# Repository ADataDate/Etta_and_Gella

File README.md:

Hardware project collaborations by Etta and Gella
=================================================================
Repository Contents
-------------------
* **/Bat** - wearable bat badge created for Fashion Hacking for Augmented Identity workshop SXSW 2019 
* **/BigBat** - large bat shaped development board prototype
* **/Diamond** - modular wearable hardware prototype for Designing Expressive Modular Hardware workshop Hackaday Superconference 2019
 
Released under: `https://creativecommons.org/licenses/by-nc-sa/4.0/legalcode

This license lets others remix, tweak, and build upon your work
non-commercially, and although their new works must also 
acknowledge you and be non-commercial, they don’t have to
 license their derivative works on the same terms.

Keep in touch with us:
* Mary [@_LightningHawk](https://twitter.com/_LightningHawk), https://www.ettawest.com
* Angela [@the_gella](https://twitter.com/the_gella), https://gellacraft.com

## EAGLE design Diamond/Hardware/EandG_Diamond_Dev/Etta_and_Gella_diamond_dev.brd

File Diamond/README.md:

Designing Expressive Modular Wearable Hardware
with Etta and Gella @ Hackaday Superconference November 2, 2018 

=================================================================

Repository Contents
-------------------
* **/Firmware** - Example code 
* **/Hardware** - Eagle design files (.brd, .sch)
* **/Spreadsheets** - BOM, parts and boards tracking, etc.
* **/Graphics** - Brainstorming images, sketches, laser files
 
Released under: `https://creativecommons.org/licenses/by-nc-sa/4.0/legalcode

This license lets others remix, tweak, and build upon your work
non-commercially, and although their new works must also 
acknowledge you and be non-commercial, they don’t have to
 license their derivative works on the same terms.

[Workshop slides](https://docs.google.com/presentation/d/1X1z0bJy7SYfVST1Kgu7OEDOKLFOzCg2_WMVUaLJVd0Q/edit?usp=sharing)

Keep in touch with us:
* Mary [@_LightningHawk](https://twitter.com/_LightningHawk), https://www.ettawest.com
* Angela [@the_gella](https://twitter.com/the_gella), https://gellacraft.com

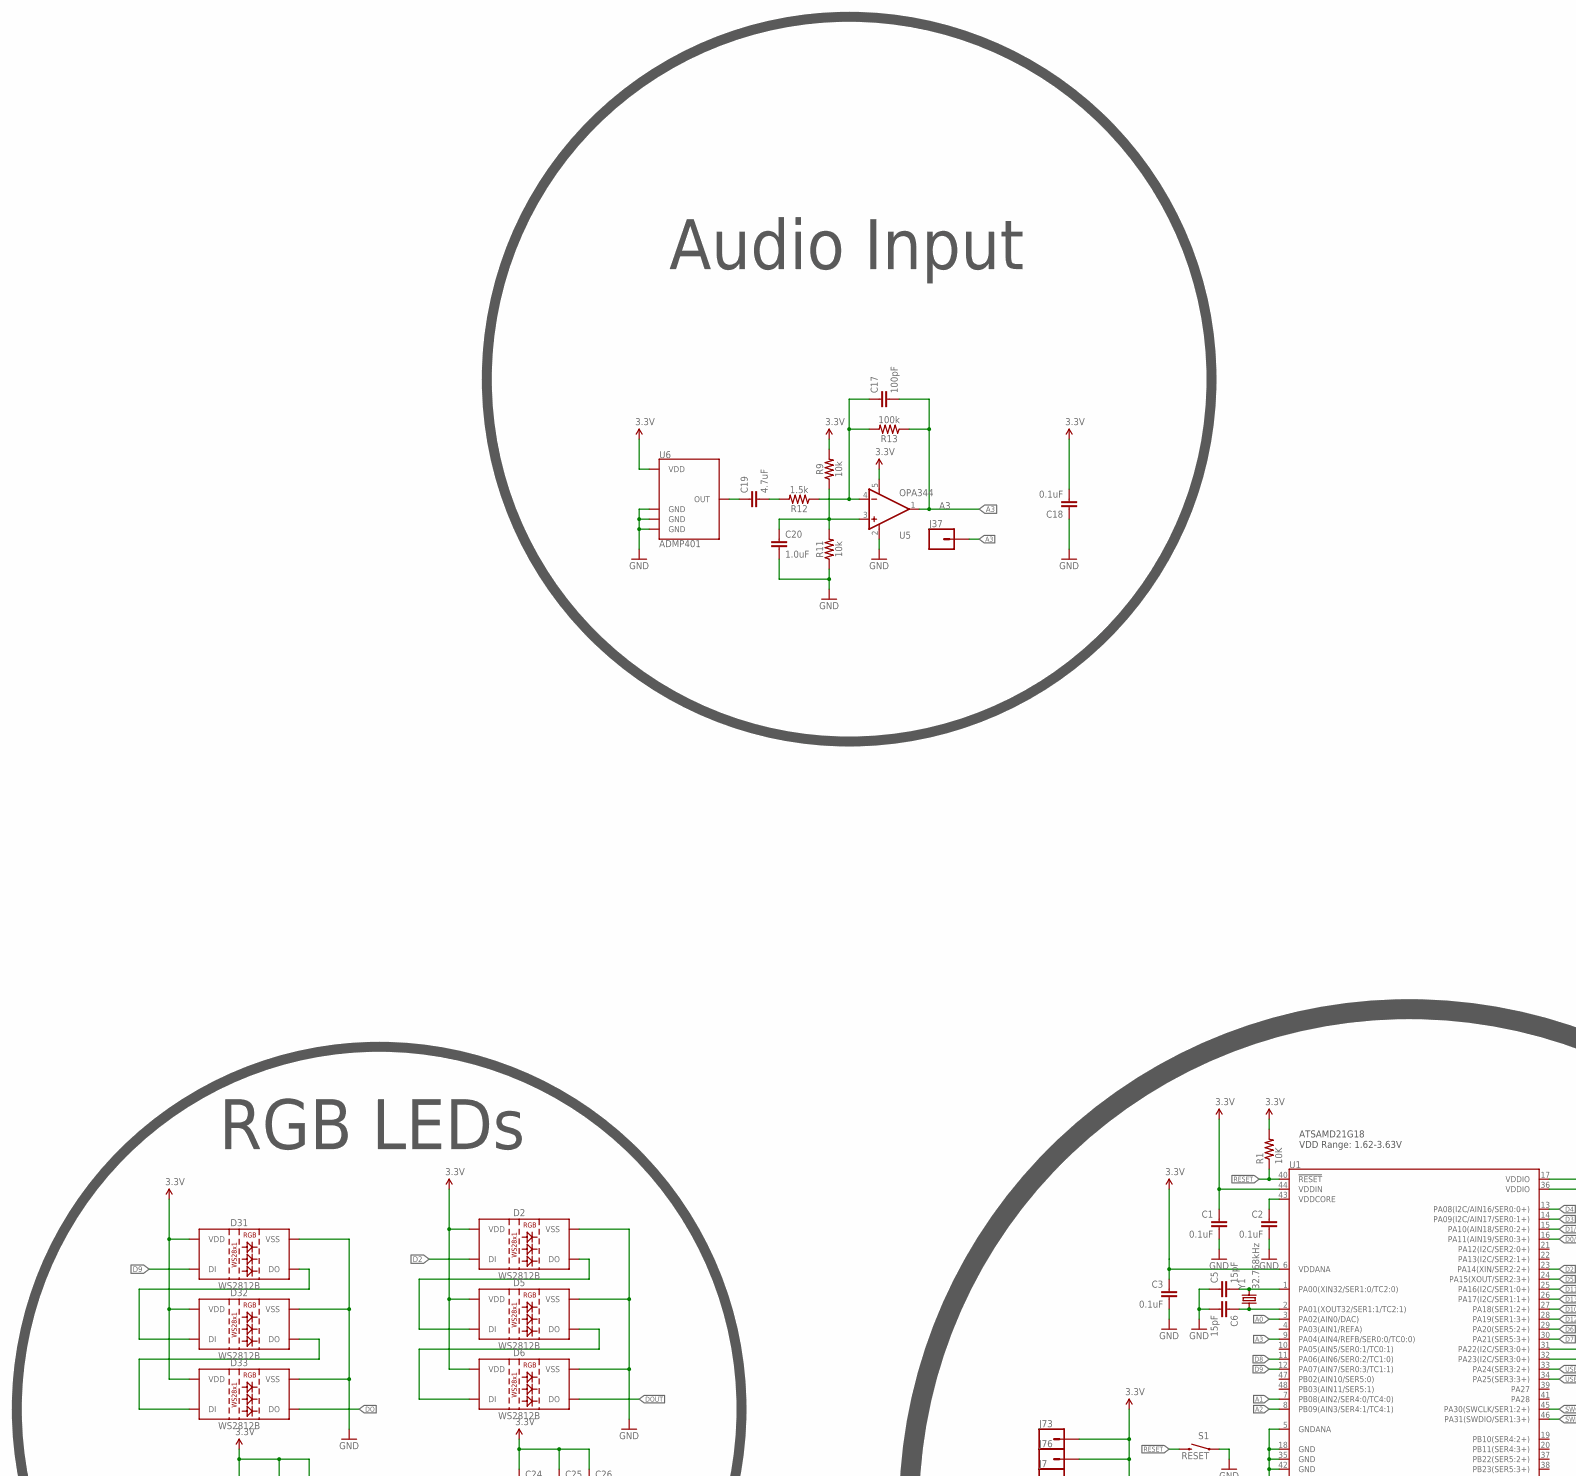
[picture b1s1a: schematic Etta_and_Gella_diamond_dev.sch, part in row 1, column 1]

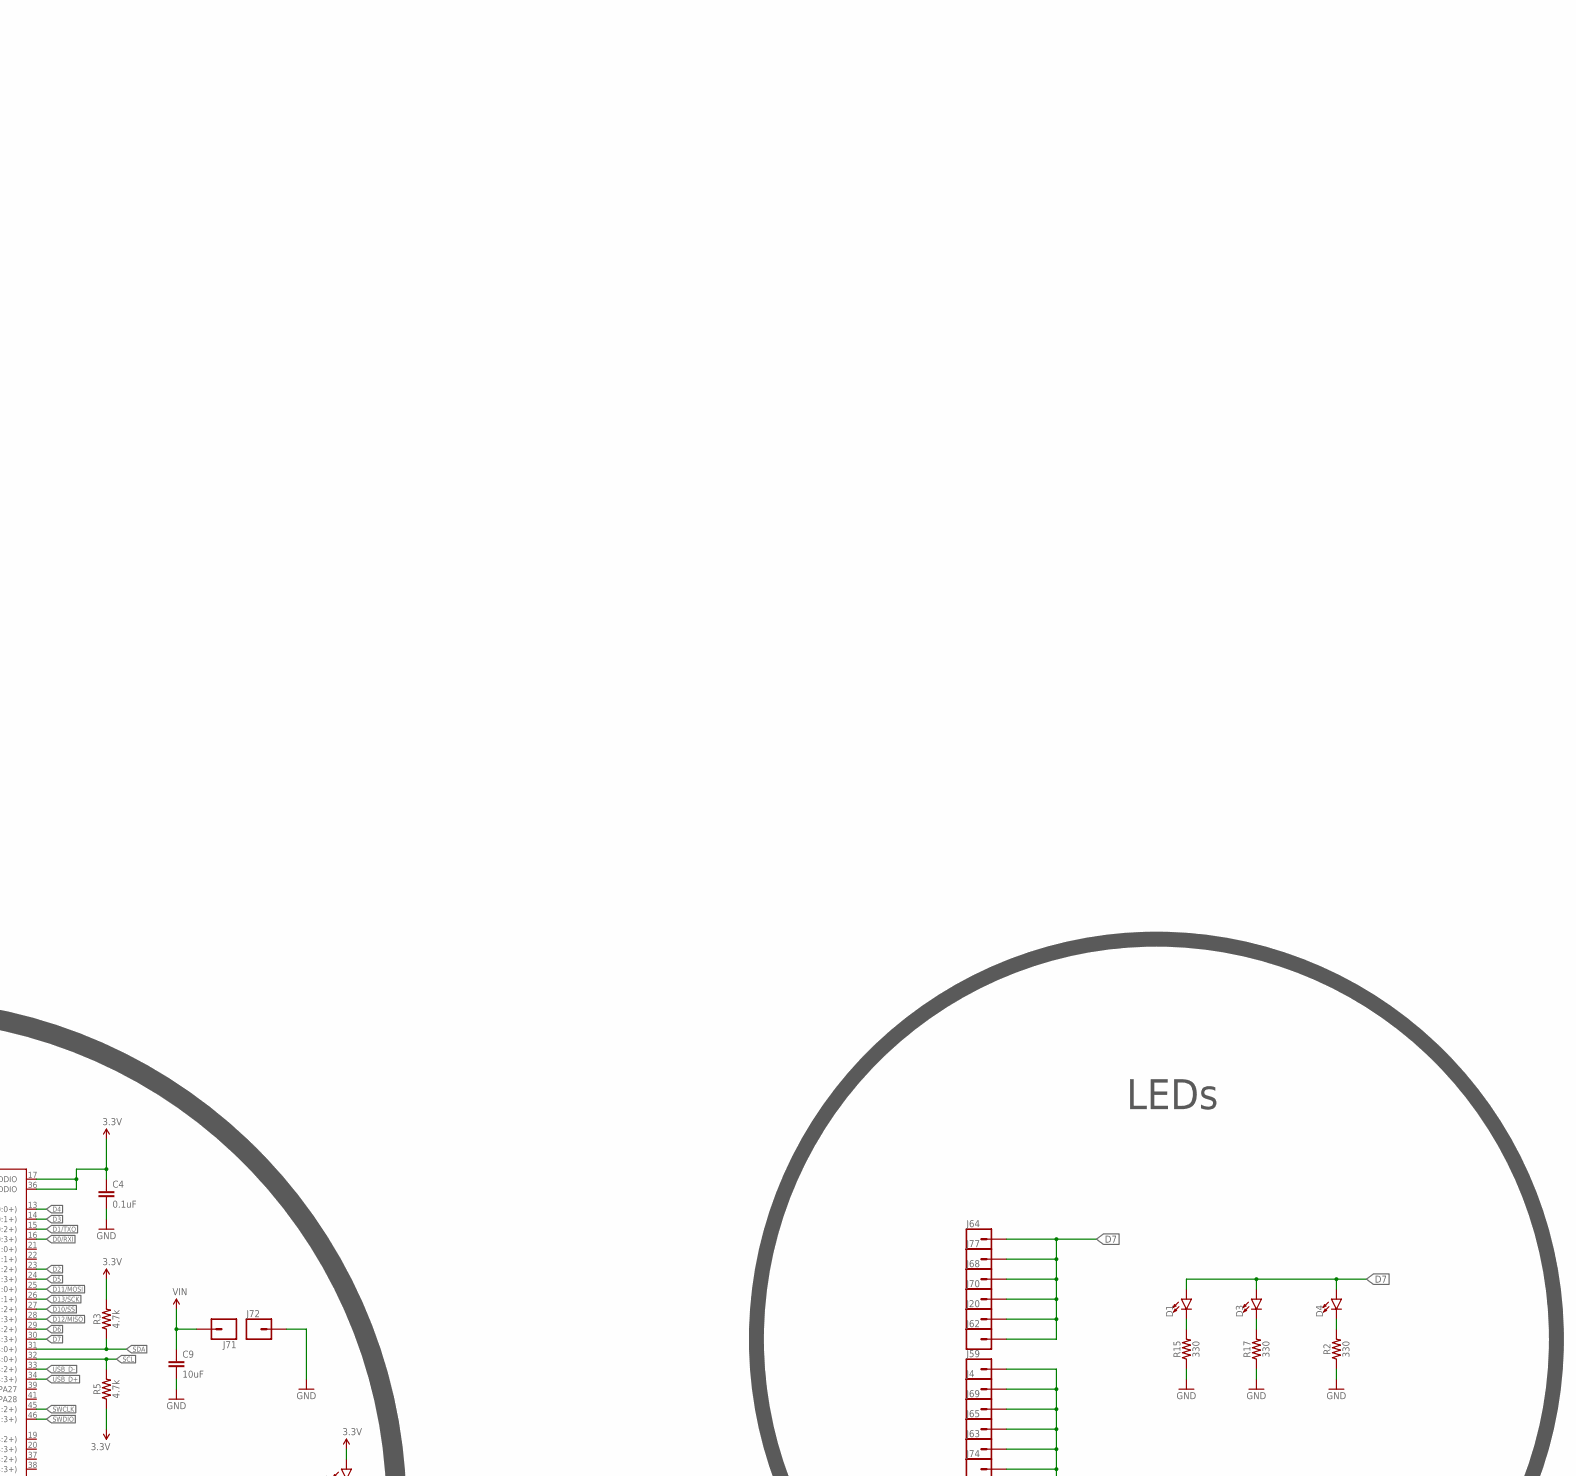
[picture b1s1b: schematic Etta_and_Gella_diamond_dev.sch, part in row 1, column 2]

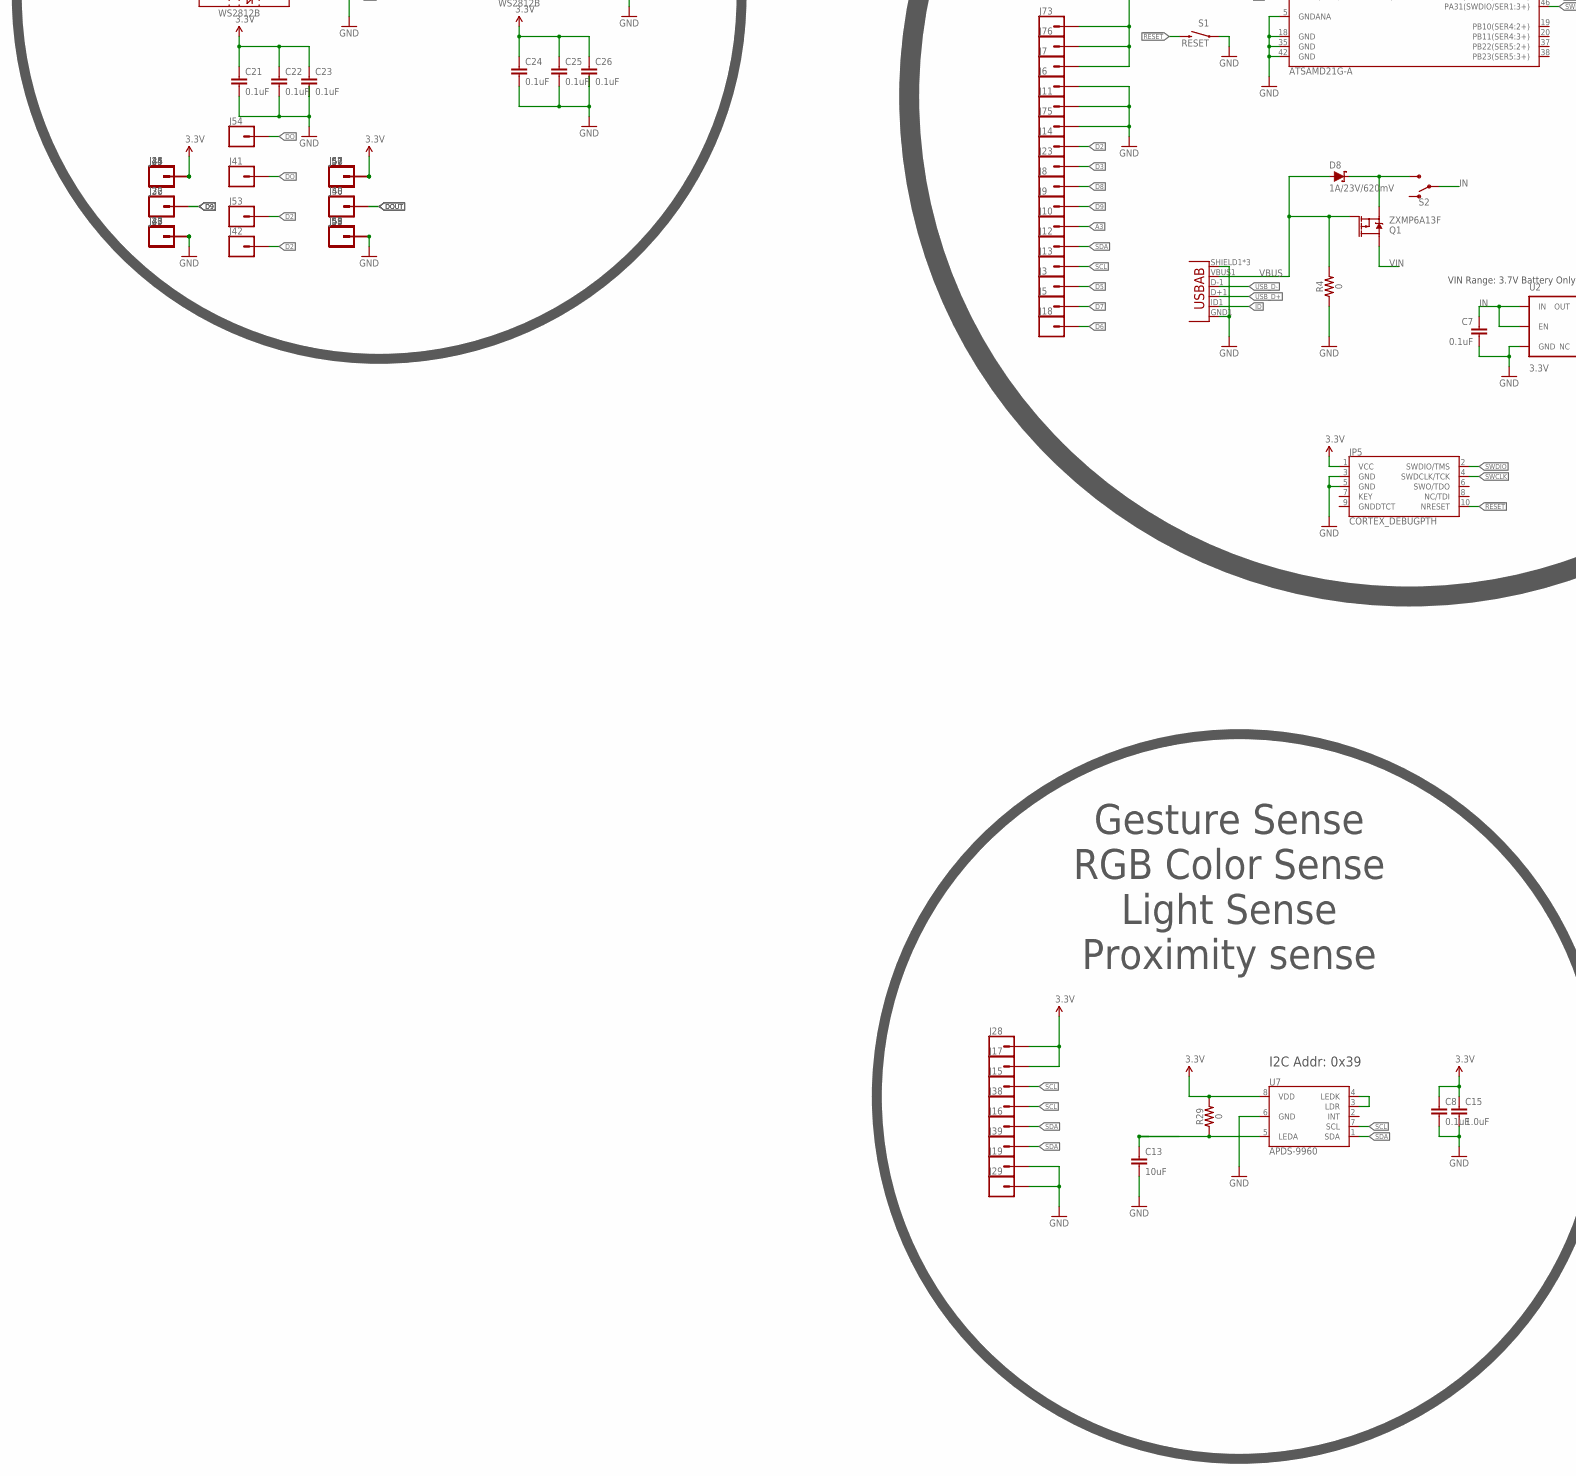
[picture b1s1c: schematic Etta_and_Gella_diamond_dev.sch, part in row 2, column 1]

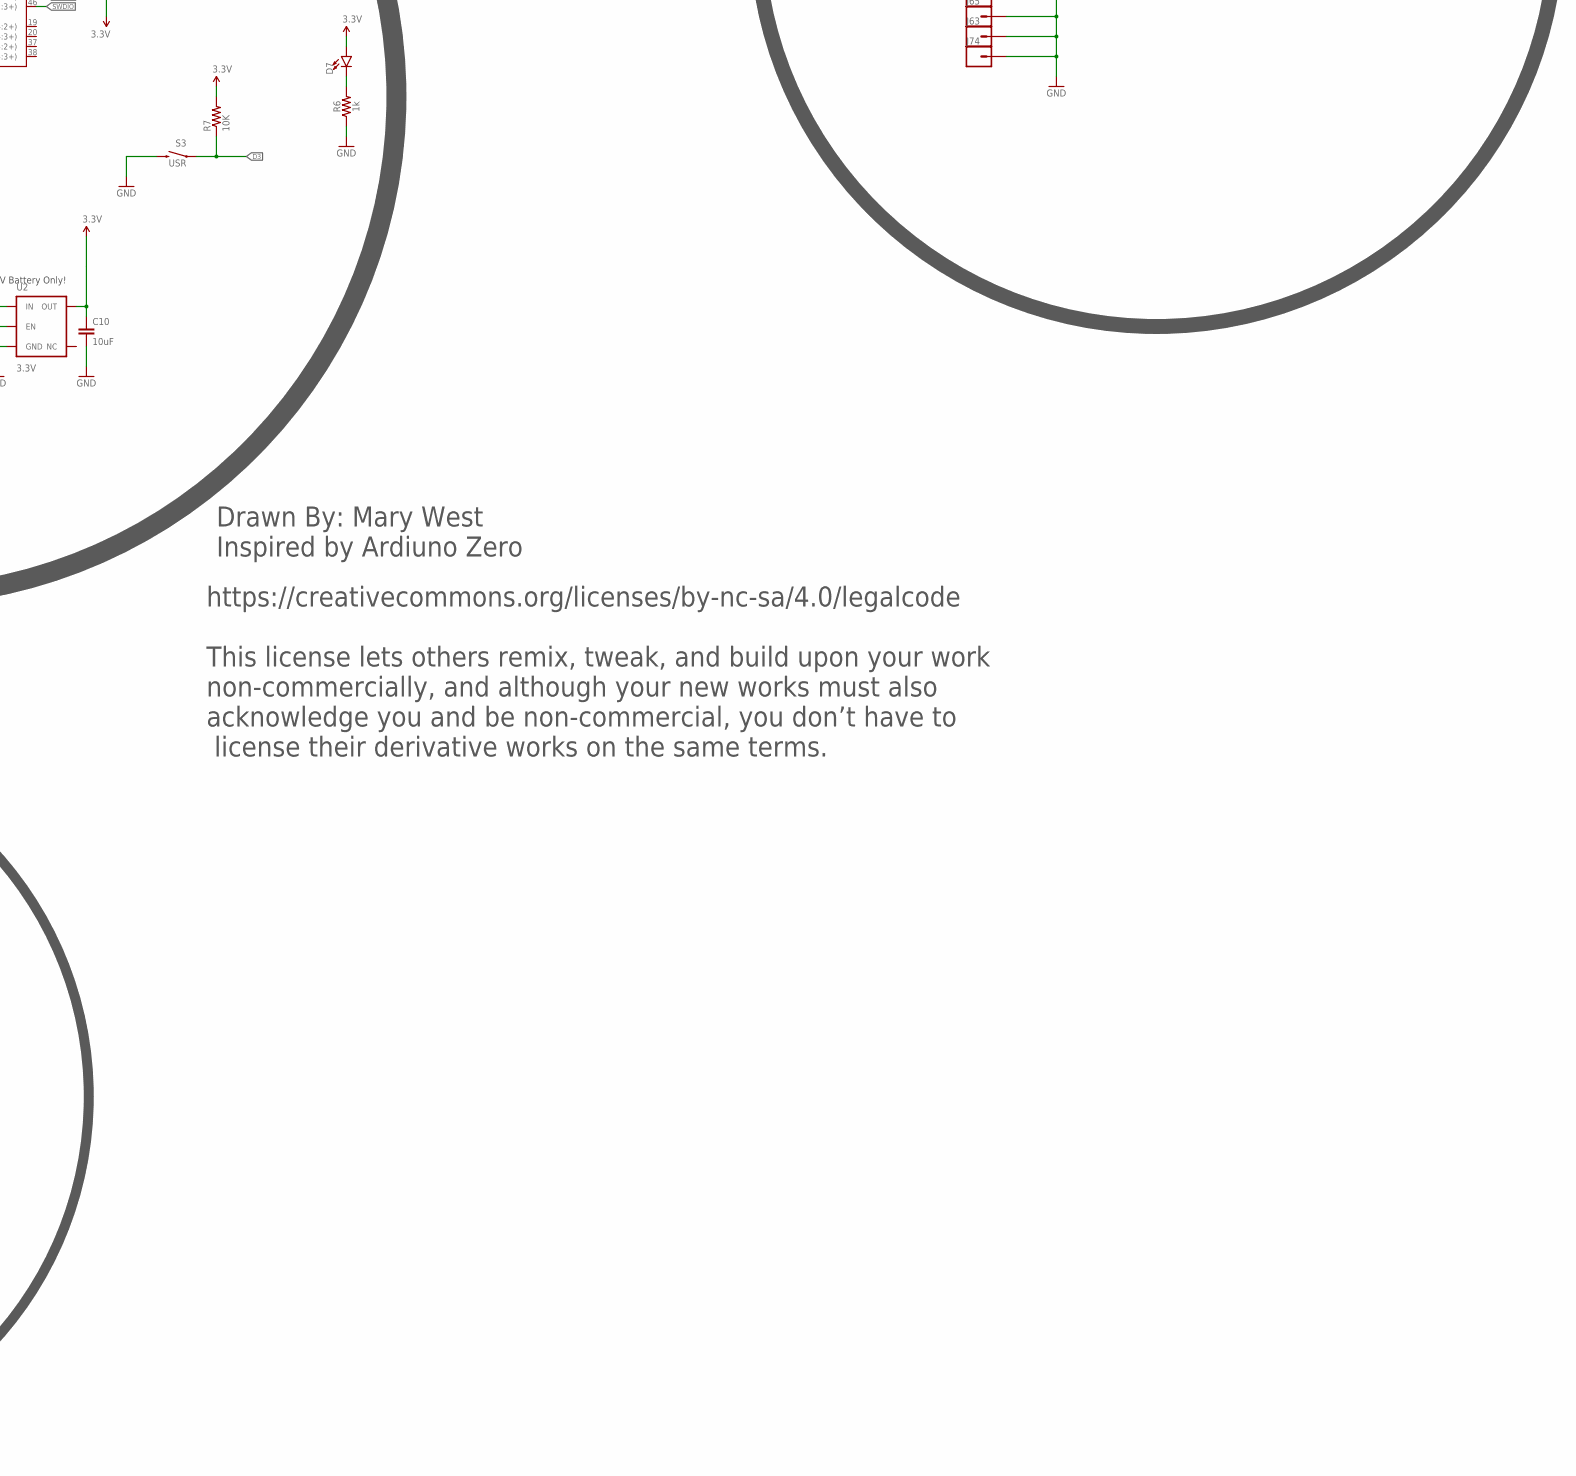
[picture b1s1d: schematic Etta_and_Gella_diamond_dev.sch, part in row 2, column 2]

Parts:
C1, C2, C3, C4, C7, C8, C18, C21, C22, C23, C24, C25, C26: 0.1uF; 0603
C5, C6: 15pF; 0603
C9, C10: 10uF; 0603
C13: 10uF; 0805
C15, C20: 1.0uF; 0603
C17: 100pF; 0603
C19: 4.7uF; 0603
D1, D3, D4, D7: LED1206; LED-1206
D2, D5, D6, D31, D32, D33: WS2812B
D8: 1A/23V/620mV; SOD-323
J3, J4, J5, J6, J7, J8, J9, J10, J11, J12, J13, J14, J15, J16, J17, J18, J19, J20, J23, J25, J26, J27, J28, J29, J32, J33, J34, J37, J38, J39, J41, J42, J43, J44, J45, J46, J47, J48, J49, J50, J51, J52, J53, J54, J55, J56, J57, J58, J59, J62, J63, J64, J65, J68, J69, J70, J71, J72, J73, J74, J75, J76, J77: CONN_01; 1X01
JP3: USB-ABCONN-11794; USB-AB-MICRO-SMD_V03
JP5: CORTEX_DEBUGPTH; 2X5-PTH-1.27MM
Q1: ZXMP6A13F; SOT23-3
R1, R7: 10K; 0603-RES@1
R2, R15, R17: 330; 0603
R3, R5: 4.7k; 0603
R4, R29: 0; 0603
R6: 1k; 0603
R9, R11: 10k; 0603
R12: 1.5k; 0603
R13: 100k; 0603
S1: RESET; TACTILE_SWITCH_SMD_4.6X2.8MM
S2: SWITCH-SPDT-SMD-AYZ0202; SWITCH_DPDT_SMD_AYZ0202
S3: USR; TACTILE_SWITCH_SMD_4.6X2.8MM
U1: ATSAMD21G-A; TQFP-48
U2: 3.3V; SOT23-5
U5: OPA344; SOT23-5
U6: ADMP401
U7: APDS-9960
Y1: 32.768kHz; CRYSTAL-SMD-3.2X1.5MM

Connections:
3.3V: C1.1, C3.1, C4.1, C8.1, C10.1, C15.1, C18.2, C21.1, C22.1, C23.1, C24.1, C25.1, C26.1, D2.1 (VDD), D5.1 (VDD), D6.1 (VDD), D7.A, D31.1 (VDD), D32.1 (VDD), D33.1 (VDD), J7.P$1, J17.P$1, J25.P$1, J28.P$1, J34.P$1, J44.P$1, J45.P$1, J47.P$1, J52.P$1, J56.P$1, J57.P$1, J73.P$1, J76.P$1, JP5.1 (VCC), R1.2, R3.2, R5.1, R7.2, R9.2, R29.2, U1.6 (VDDANA), U1.17 (VDDIO), U1.36 (VDDIO), U1.44 (VDDIN), U2.5 (OUT), U5.5 (V+), U6.5 (VDD), U7.8 (VDD)
!RESET: JP5.10 (NRESET), R1.1, S1.3 (2), S1.4 (2), U1.40 (!RESET!)
A0: U1.3 (PA02(AIN0/DAC))
A1: U1.7 (PB08(AIN2/SER4:0/TC4:0))
A2: U1.8 (PB09(AIN3/SER4:1/TC4:1))
A3: C17.2, J10.P$1, J37.P$1, R13.1, U1.9 (PA04(AIN4/REFB/SER0:0/TC0:0)), U5.1 (OUT)
D0/RXI: U1.16 (PA11(AIN19/SER0:3+))
D1/TXO: U1.15 (PA10(AIN18/SER0:2+))
D2: D2.4 (DI), J14.P$1, J42.P$1, J53.P$1, U1.23 (PA14(XIN/SER2:2+))
D3: J23.P$1, R7.1, S3.1, S3.2 (1), U1.14 (PA09(I2C/AIN17/SER0:1+))
D4: U1.13 (PA08(I2C/AIN16/SER0:0+))
D5: J3.P$1, U1.24 (PA15(XOUT/SER2:3+))
D6: J18.P$1, U1.29 (PA20(SER5:2+))
D7: D1.A, D3.A, D4.A, J5.P$1, J20.P$1, J62.P$1, J64.P$1, J68.P$1, J70.P$1, J77.P$1, U1.30 (PA21(SER5:3+))
D8: J8.P$1, U1.11 (PA06(AIN6/SER0:2/TC1:0))
D9: D31.4 (DI), J9.P$1, J26.P$1, J32.P$1, U1.12 (PA07(AIN7/SER0:3/TC1:1))
D10/SS: U1.27 (PA18(SER1:2+))
D11/MOSI: U1.25 (PA16(I2C/SER1:0+))
D12/MISO: U1.28 (PA19(SER1:3+))
D13/SCK: U1.26 (PA17(I2C/SER1:1+))
DO: D33.2 (DO), J41.P$1, J54.P$1
DOUT: D6.2 (DO), J48.P$1, J50.P$1
GND: C1.2, C2.2, C3.2, C4.2, C5.1, C6.2, C7.2, C8.2, C9.2, C10.2, C13.2, C15.2, C18.1, C20.2, C21.2, C22.2, C23.2, C24.2, C25.2, C26.2, D2.3 (VSS), D5.3 (VSS), D6.3 (VSS), D31.3 (VSS), D32.3 (VSS), D33.3 (VSS), J4.P$1, J6.P$1, J11.P$1, J19.P$1, J27.P$1, J29.P$1, J33.P$1, J43.P$1, J46.P$1, J49.P$1, J51.P$1, J55.P$1, J58.P$1, J59.P$1, J63.P$1, J65.P$1, J69.P$1, J72.P$1, J74.P$1, J75.P$1, JP3.GND1 (GND), JP3.SHIELD1 (SHIELD), JP3.SHIELD2 (SHIELD), JP3.SHIELD3 (SHIELD), JP5.3 (GND), JP5.5 (GND), R2.1, R4.1, R6.1, R11.1, R15.1, R17.1, S1.1, S1.2 (1), S3.3 (2), S3.4 (2), U1.5 (GNDANA), U1.18 (GND), U1.35 (GND), U1.42 (GND), U2.2 (GND), U5.2 (V-), U6.2 (GND), U6.4 (GND), U6.6 (GND), U7.6 (GND)
ID: JP3.ID1 (USBID)
IN: C7.1, S2.2, U2.1 (IN), U2.3 (EN)
LEDA: C13.1, R29.1, U7.5 (LEDA)
unnamed: D4.C, R2.2
unnamed: C5.2, U1.1 (PA00(XIN32/SER1:0/TC2:0)), Y1.P$2 (2)
unnamed: C19.1, U6.1 (OUT)
unnamed: C6.1, U1.2 (PA01(XOUT32/SER1:1/TC2:1)), Y1.P$1 (1)
unnamed: U7.3 (LDR), U7.4 (LEDK)
unnamed: C17.1, R12.1, R13.2, U5.4 (-IN)
unnamed: D7.C, R6.2
unnamed: D8.C, Q1.2 (S), S2.3 (S)
unnamed: C19.2, R12.2
unnamed: C20.1, R9.1, R11.2, U5.3 (+IN)
unnamed: D1.C, R15.2
unnamed: D31.2 (DO), D32.4 (DI)
unnamed: D3.C, R17.2
unnamed: D32.2 (DO), D33.4 (DI)
unnamed: D2.2 (DO), D5.4 (DI)
unnamed: D5.2 (DO), D6.4 (DI)
SCL: J13.P$1, J15.P$1, J38.P$1, R5.2, U1.32 (PA23(I2C/SER3:0+)), U7.7 (SCL)
SDA: J12.P$1, J16.P$1, J39.P$1, R3.1, U1.31 (PA22(I2C/SER3:0+)), U7.1 (SDA)
SWCLK: JP5.4 (SWDCLK/TCK), U1.45 (PA30(SWCLK/SER1:2+))
SWDIO: JP5.2 (SWDIO/TMS), U1.46 (PA31(SWDIO/SER1:3+))
USB_D+: JP3.D+1 (D+), U1.34 (PA25(SER3:3+))
USB_D-: JP3.D-1 (D-), U1.33 (PA24(SER3:2+))
VBUS: D8.A, JP3.VBUS1 (VBUS), Q1.1 (G), R4.2
VDDCORE: C2.1, U1.43 (VDDCORE)
VIN: C9.1, J71.P$1, Q1.3 (D)

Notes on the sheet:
ATSAMD21G18 VDD Range: 1.62-3.63V
VIN Range: 3.7V Battery Only!
LEDs
Audio Input
Gesture Sense RGB Color Sense Light Sense Proximity sense
I2C Addr: 0x39
RGB LEDs
https://creativecommons.org/licenses/by-nc-sa/4.0/legalcode This license lets others remix, tweak, and build upon your work non-commercially, and although your new works must also acknowledge you and be non-commercial, you don’t have to license their derivative works on the same terms.
Drawn By: Mary West Inspired by Ardiuno Zero

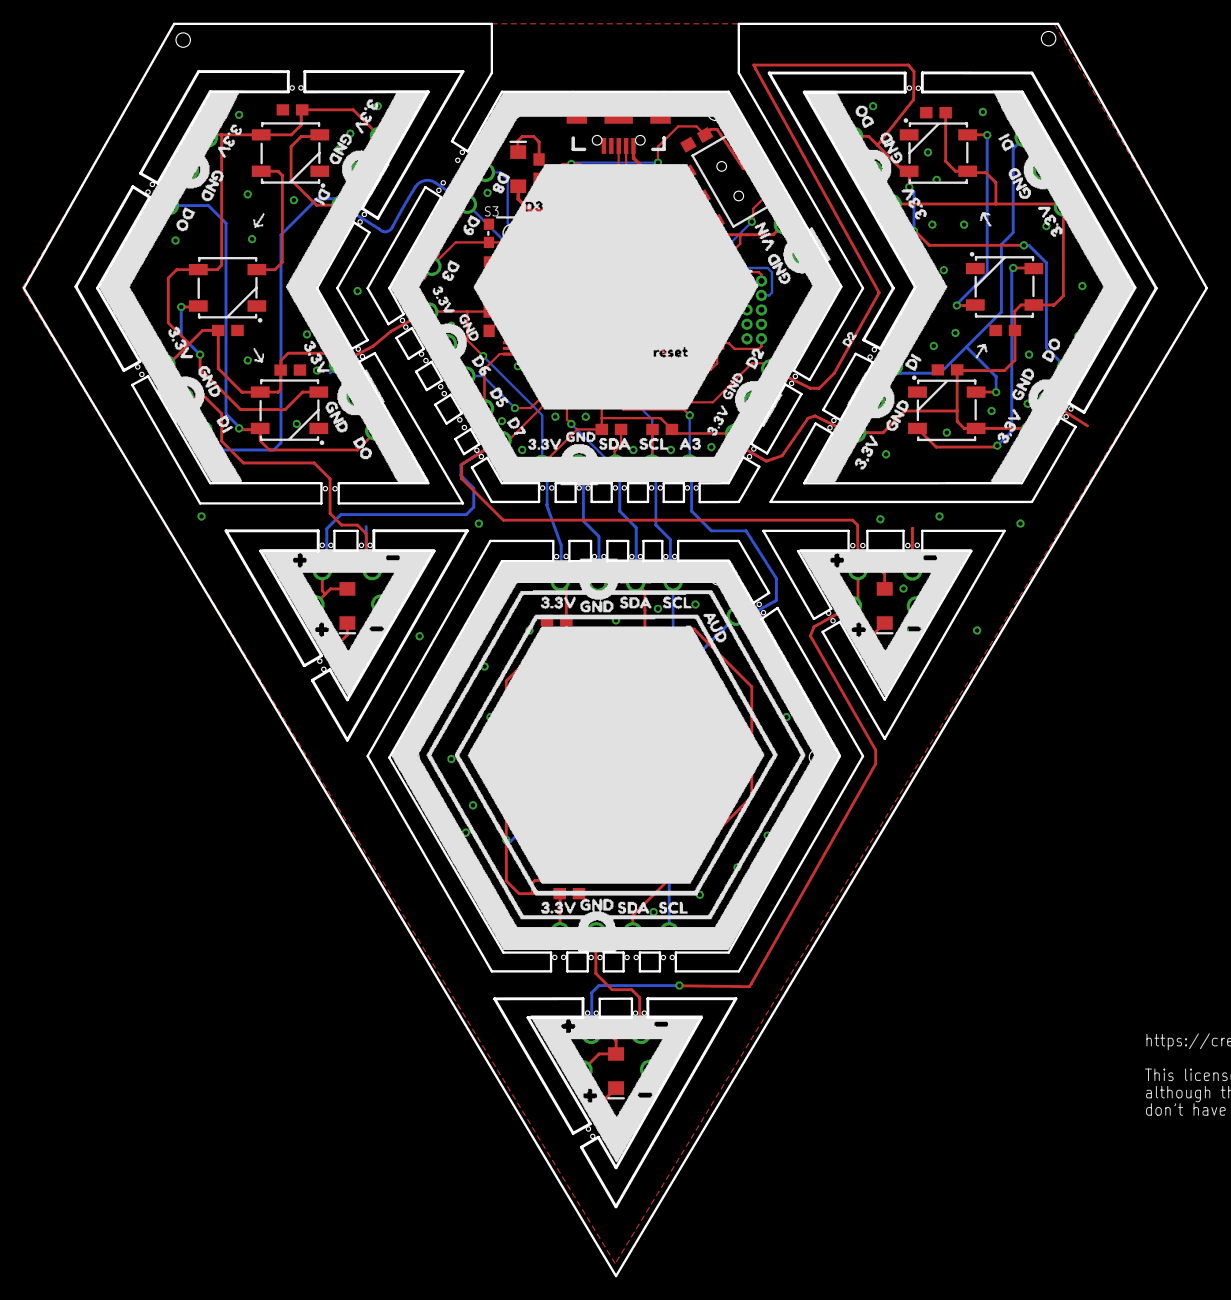
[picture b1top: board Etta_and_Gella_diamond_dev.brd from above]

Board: 2 copper layers, 104.0 x 110.1 mm, 125 parts (0 on the bottom side), 40 nets.

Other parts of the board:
U$1: A5L-LOC
U$2: HACKMODWEAR_V2SILK_DRAFT_BUZZARDTOP#01#JPG
U$3: HACKMODWEAR_V2SILK_DRAFT_BUZZARDBOTTOM#01#JPG

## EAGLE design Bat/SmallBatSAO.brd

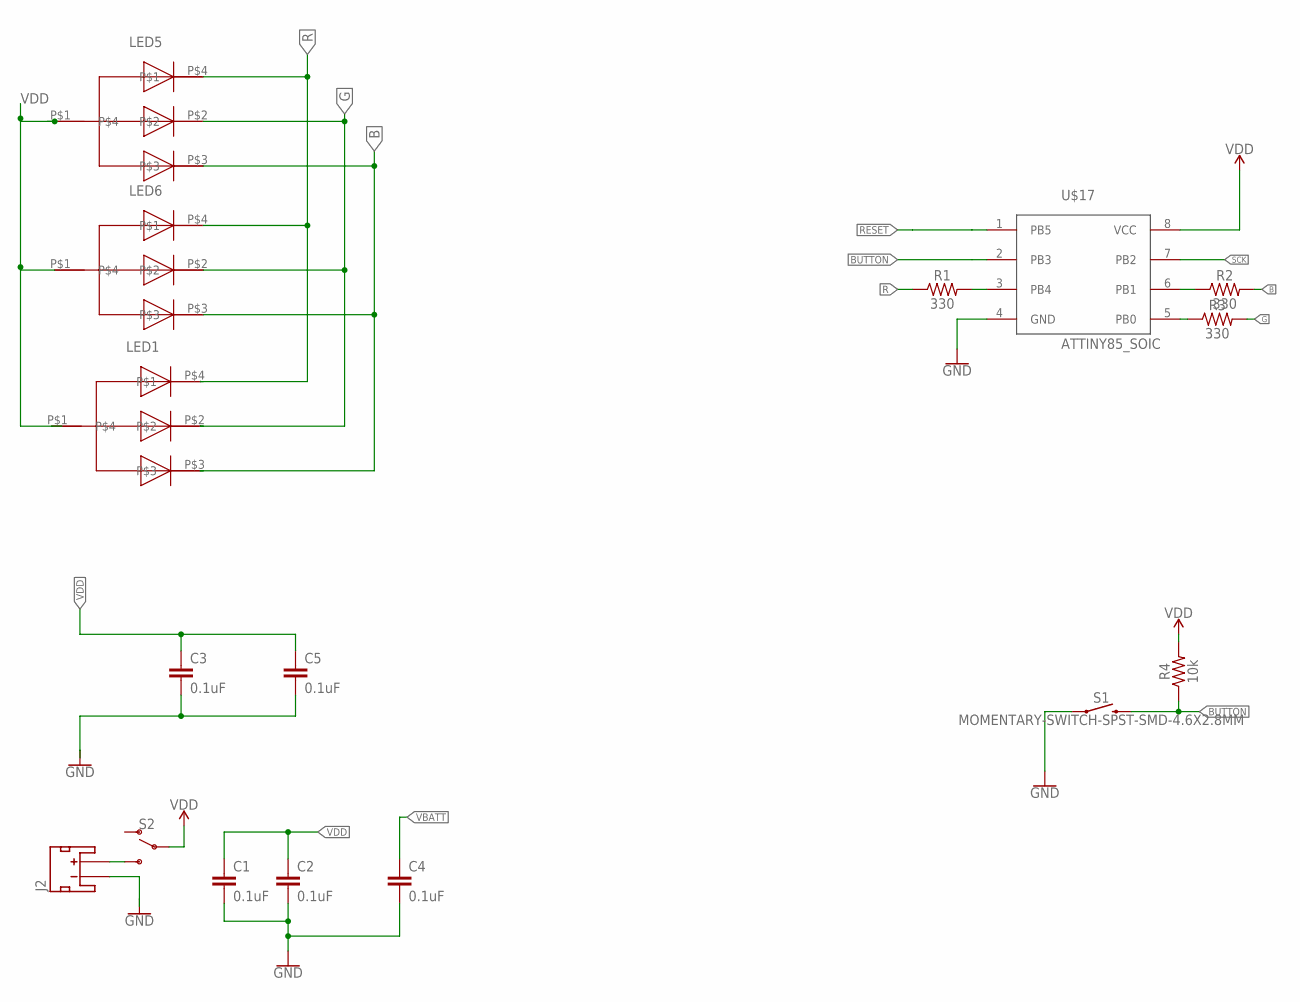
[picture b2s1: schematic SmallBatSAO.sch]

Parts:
C1, C2, C3, C4, C5: 0.1uF; 0603
J2: JST_2MM_MALE; JST-2-SMD
LED1, LED5, LED6: PLCC4_REVERSE_MOUNT; PLCC4_SMD_REVERSE_MOUNT_LED
R1, R2, R3: 330; 0603
R4: 10k; 0603
S1: MOMENTARY-SWITCH-SPST-SMD-4.6X2.8MM; TACTILE_SWITCH_SMD_4.6X2.8MM
S2: SWITCH-SPDT-SMD-AYZ0202; SWITCH_DPDT_SMD_AYZ0202
U$17: ATTINY85_SOIC; SOIC-8

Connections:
B: LED1.P$3, LED5.P$3, LED6.P$3, R2.2
BUTTON: R4.1, S1.3 (2), S1.4 (2), U$17.2 (PB3)
G: LED1.P$2, LED5.P$2, LED6.P$2, R3.2
GND: C1.2, C2.2, C3.2, C4.2, C5.2, J2.1 (-), S1.1, S1.2 (1), U$17.4 (GND)
unnamed: R2.1, U$17.6 (PB1)
unnamed: R3.1, U$17.5 (PB0)
unnamed: R1.2, U$17.3 (PB4)
R: LED1.P$4, LED5.P$4, LED6.P$4, R1.1
RESET: U$17.1 (PB5)
SCK: U$17.7 (PB2)
VBATT: C4.1, J2.2 (+), S2.3 (S)
VDD: C1.1, C2.1, C3.1, C5.1, LED1.P$1, LED5.P$1, LED6.P$1, R4.2, S2.2, U$17.8 (VCC)

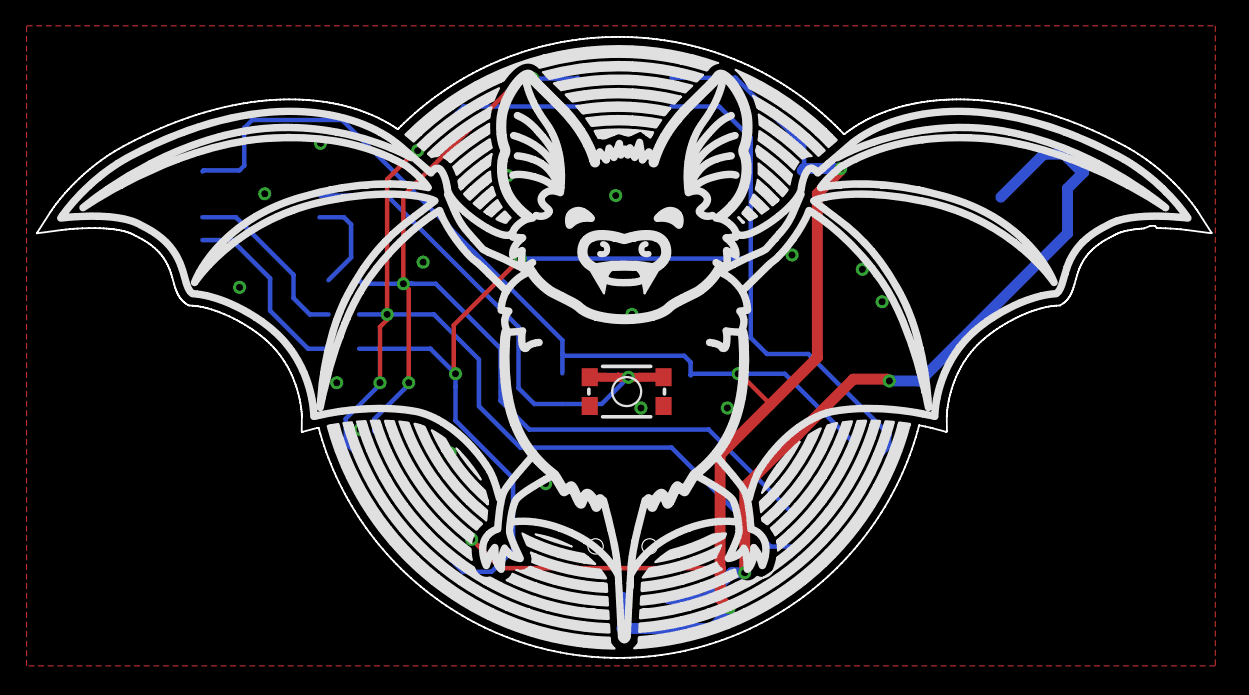
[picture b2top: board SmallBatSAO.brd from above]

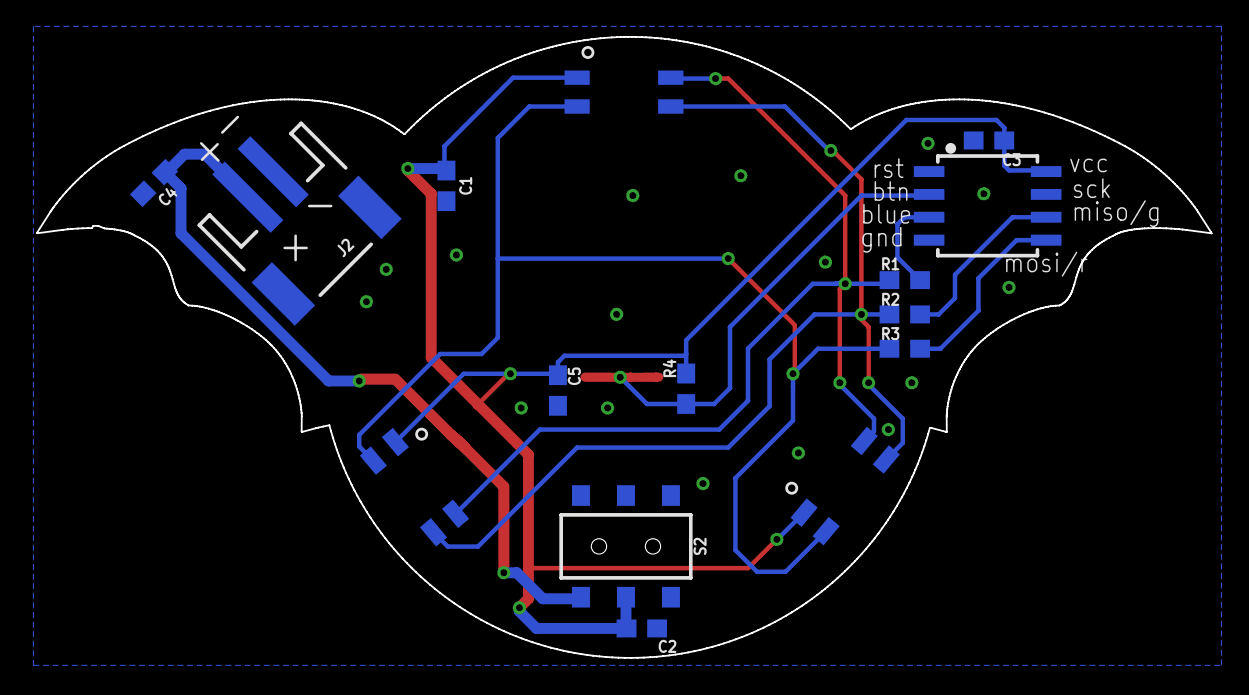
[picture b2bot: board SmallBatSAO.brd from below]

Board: 2 copper layers, 65.3 x 34.5 mm, 16 parts (15 on the bottom side), 10 nets.

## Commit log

2018-09-30 Adding BOM and gerbers
2018-09-30 adding reamde for review notes and coms
2018-10-02 small updates
2018-10-02 removing lock file
2018-10-03 Added Google drive links
2018-10-03 Added DigiKey part #s to BOM
2018-10-04 Added Graphics folder
    Fonts for board labeling
2018-10-04 font choices (200% scale)
2018-10-05 Updated font graphic export
2018-10-07 new board design, 2 layers, removed haptic motor driver, swapped components for cheaper/smaller packages, removed USB ID, pushed back headers from board edge
2018-10-07 pusging before Eagle decides to crash again losing hours of work - thanks eagle 9 for nothing
2018-10-07 Adding gerbers
2018-10-07 Updating BOM
2018-10-07 Adding logo
2018-10-09 Added Silk rough drafts for review
2018-10-10 Playing with reference lines to standardize cut-out widths
2018-10-10 Moving bottom triangle in line with the outer dimension
2018-10-11 final component placement
2018-10-11 continuing trace routing
2018-10-11 Exported sample PNG for silk import
2018-10-11 Adding Silk Options for trial imports
2018-10-11 Adding Illustrator file
2018-10-11 72dpi export to test
2018-10-11 Size test
2018-10-11 UPdated route out
2018-10-11 Final Board layout
2018-10-11 Removed old test files, added final silk options
2018-10-11 Updated silk
2018-10-12 updated per awesome peer review
2018-10-12 final board/sch
2018-10-12 Enlarged Silk Text
2018-10-12 Added 3.3V Label option
2018-10-12 Added Larger Text VCC or 3.3V label options
2018-10-21 Illustrator working files for silk
2018-10-28 Adding example code
2018-11-02 updating README
2018-11-02 Cleaning stuff
2018-11-02 ReadME update
2018-11-02 Added contact info
2018-11-02 updated links
2018-11-02 adding new example project
2018-11-03 Adding workshop slide link
2018-12-07 making room for more projects!
2018-12-25 Updates to power supply section
2018-12-30 Diamond Shape Export Test
    From illustrator export
2018-12-30 Small Bat Export
    Dimension and silk draft
2018-12-30 Exported Big Bat Body
    Dimension, draft of tStop and silk
2018-12-30 Create BigBatWing_Left.brd
    Added Illustrator export for dimension, silk draft for left wing pcb
2018-12-30 updated to reflect new projects
2019-01-20 Bat Badge
2019-04-08 Eagle 9 giving me trouble again
2019-04-08 adding newest board
2019-04-08 moving old design file
2019-04-10 batt changes
2019-04-10 cleaning repo
2019-04-10 removing back-up files
2019-04-10 Moved LEDs to D7, changed pinout on the right chevron, etc.
2019-04-10 Create BatSAOExportTest.scr
    Added svg to eagle silk script to test in file
2019-04-11 Adding JPGs for Buzzard
    @adatadate try out the high res beta buzzard tool from Nick - https://sparkfunx.github.io/Buzzard/imgImport_HDBeta.html with these two exports to see if it can handle them. Artboard size is 107.95mm 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
2019-04-24 silk added to board

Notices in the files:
parts and their libraries:
SparkFun-Resistors: Licensing: Creative Commons ShareAlike 4.0 International - https://creativecommons.org/licenses/by-sa/4.0
